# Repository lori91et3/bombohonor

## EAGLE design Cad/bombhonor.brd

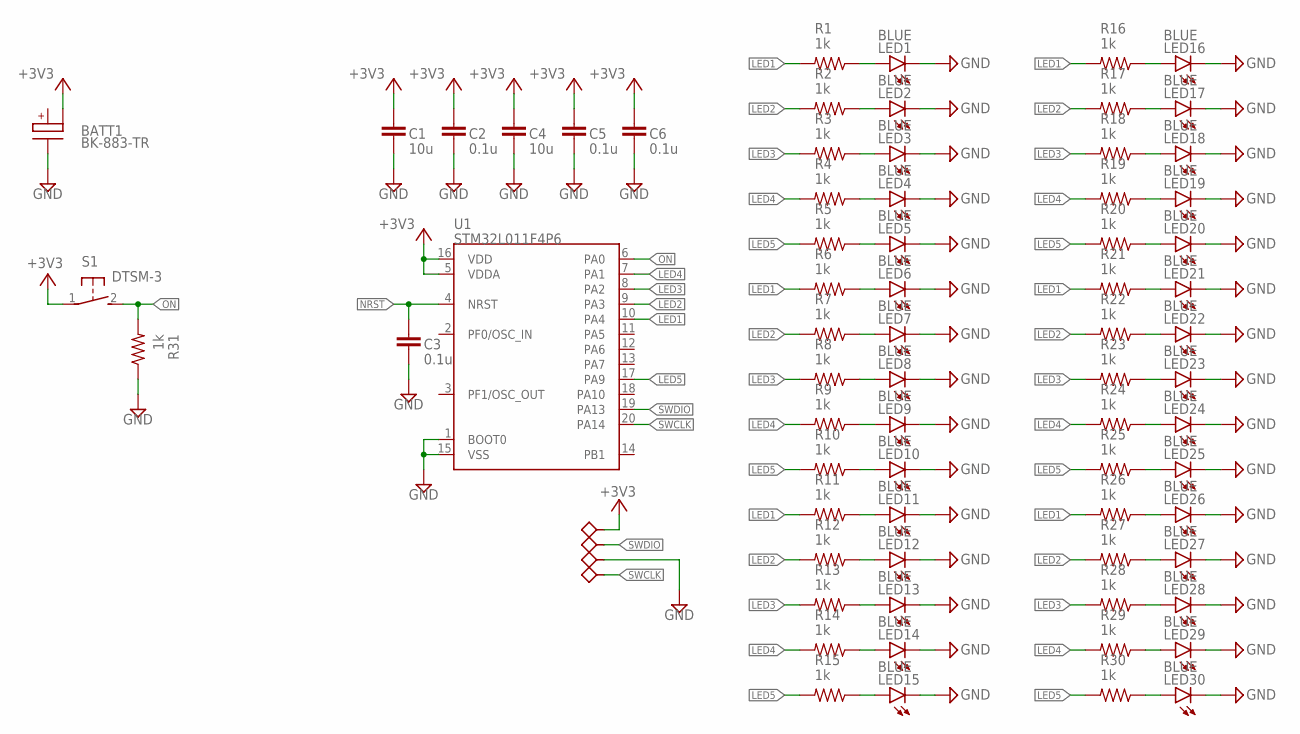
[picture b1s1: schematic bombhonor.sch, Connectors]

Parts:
BATT1: BK-883-TR; PARTNO BK-883-TR
C1, C4: 10u; 0805[2012]; PARTNO CL21A106KQCLRNC
C2, C3, C5, C6: 0.1u; 0603[1608]; PARTNO CL10B104KB8NNNC
LED1, LED2, LED3, LED4, LED5, LED6, LED7, LED8, LED9, LED10, LED11, LED12, LED13, LED14, LED15, LED16, LED17, LED18, LED19, LED20, LED21, LED22, LED23, LED24, LED25, LED26, LED27, LED28, LED29, LED30: BLUE; 1206[3216]BOTTOM_ENTRY; PARTNO LTST-C230TBKT
R1, R2, R3, R4, R5, R6, R7, R8, R9, R10, R11, R12, R13, R14, R15, R16, R17, R18, R19, R20, R21, R22, R23, R24, R25, R26, R27, R28, R29, R30, R31: 1k; 0603[1608]; PARTNO RMCF0603JT1K00
S1: DTSM-3; PARTNO DTSM-3
TP1, TP2, TP3, TP4: TESTPAD2MM; TP-2MM; PARTNO DNP
U1: STM32L011F4P6; TSSOP20; PARTNO STM32L011F4P6

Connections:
+3V3: BATT1.V+2 (V_BATT2), C1.1, C2.1, C4.1, C5.1, C6.1, S1.1, TP1.TP, U1.5 (VDDA), U1.16 (VDD)
GND: BATT1.V- (GND), C1.2, C2.2, C3.2, C4.2, C5.2, C6.2, LED1.K, LED2.K, LED3.K, LED4.K, LED5.K, LED6.K, LED7.K, LED8.K, LED9.K, LED10.K, LED11.K, LED12.K, LED13.K, LED14.K, LED15.K, LED16.K, LED17.K, LED18.K, LED19.K, LED20.K, LED21.K, LED22.K, LED23.K, LED24.K, LED25.K, LED26.K, LED27.K, LED28.K, LED29.K, LED30.K, R31.1, TP3.TP, U1.1 (BOOT0), U1.15 (VSS)
LED1: R1.2, R6.2, R11.2, R16.2, R21.2, R26.2, U1.10 (PA4)
LED2: R2.2, R7.2, R12.2, R17.2, R22.2, R27.2, U1.9 (PA3)
LED3: R3.2, R8.2, R13.2, R18.2, R23.2, R28.2, U1.8 (PA2)
LED4: R4.2, R9.2, R14.2, R19.2, R24.2, R29.2, U1.7 (PA1)
LED5: R5.2, R10.2, R15.2, R20.2, R25.2, R30.2, U1.17 (PA9)
unnamed: LED1.A, R1.1
unnamed: LED2.A, R2.1
unnamed: LED3.A, R3.1
unnamed: LED4.A, R4.1
unnamed: LED5.A, R5.1
unnamed: LED6.A, R6.1
unnamed: LED7.A, R7.1
unnamed: LED8.A, R8.1
unnamed: LED9.A, R9.1
unnamed: LED10.A, R10.1
unnamed: LED11.A, R11.1
unnamed: LED12.A, R12.1
unnamed: LED13.A, R13.1
unnamed: LED14.A, R14.1
unnamed: LED15.A, R15.1
unnamed: LED16.A, R16.1
unnamed: LED17.A, R17.1
unnamed: LED18.A, R18.1
unnamed: LED19.A, R19.1
unnamed: LED20.A, R20.1
unnamed: LED21.A, R21.1
unnamed: LED22.A, R22.1
unnamed: LED23.A, R23.1
unnamed: LED24.A, R24.1
unnamed: LED25.A, R25.1
unnamed: LED26.A, R26.1
unnamed: LED27.A, R27.1
unnamed: LED28.A, R28.1
unnamed: LED29.A, R29.1
unnamed: LED30.A, R30.1
NRST: C3.1, U1.4 (NRST)
ON: R31.2, S1.2, U1.6 (PA0)
SWCLK: TP4.TP, U1.20 (PA14)
SWDIO: TP2.TP, U1.19 (PA13)

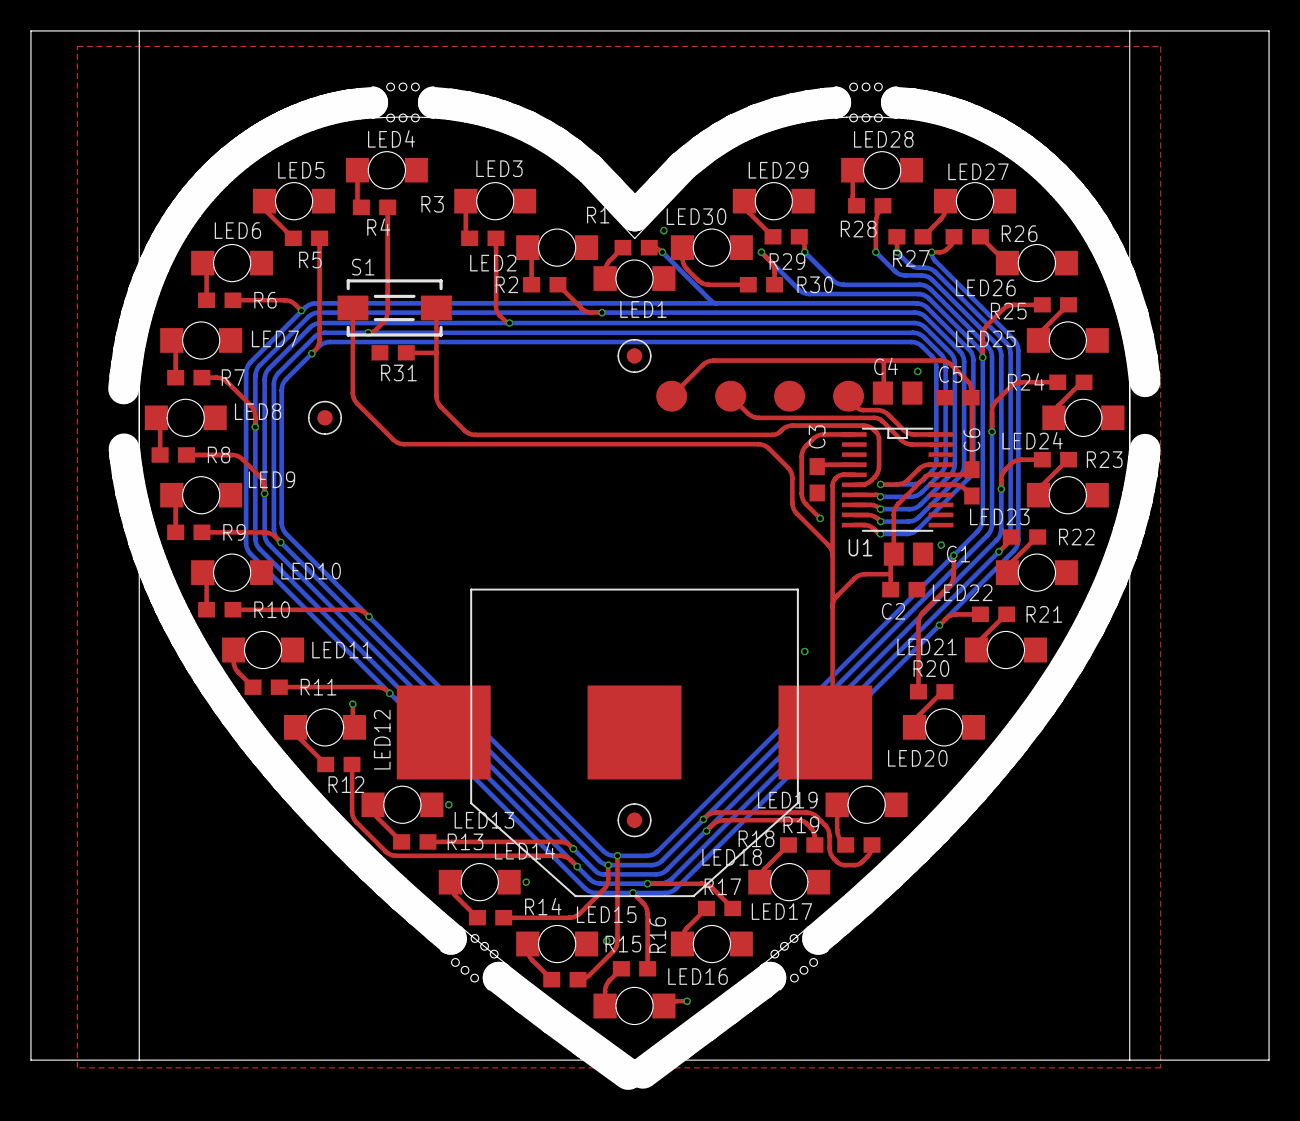
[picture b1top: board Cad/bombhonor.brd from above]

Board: 2 copper layers, 80.0 x 67.4 mm, 82 parts (1 on the bottom side), 41 nets.

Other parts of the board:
1, 2: MOUSE_BITE_2MM
U$1, U$2: MOUSE_BITE_2MM
U$3, U$4, U$5: FIDUCIAL_1MM+2MM+CREAM
U$6: SCRITTA2

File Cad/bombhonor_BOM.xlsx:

Qty | Qty to order | Value | Part Num |  | tot componenti | spesa | 185
4 | 720 | 0.1u | CL10B104KB8NNNC |  | 740
31 | 5580 | 1k | RMCF0603JT1K00 |  | 5735
2 | 360 | 10u | CL21A106KQCLRNC |  | 370
30 | 5400 | BLUE | LTST-C230TBKT |  | 5550
1 | 180 | STM32L011F4P6 | STM32L011F4P6 |  | 185
1 | 180 | BK-883-TR | BK-883-TR |  | 185

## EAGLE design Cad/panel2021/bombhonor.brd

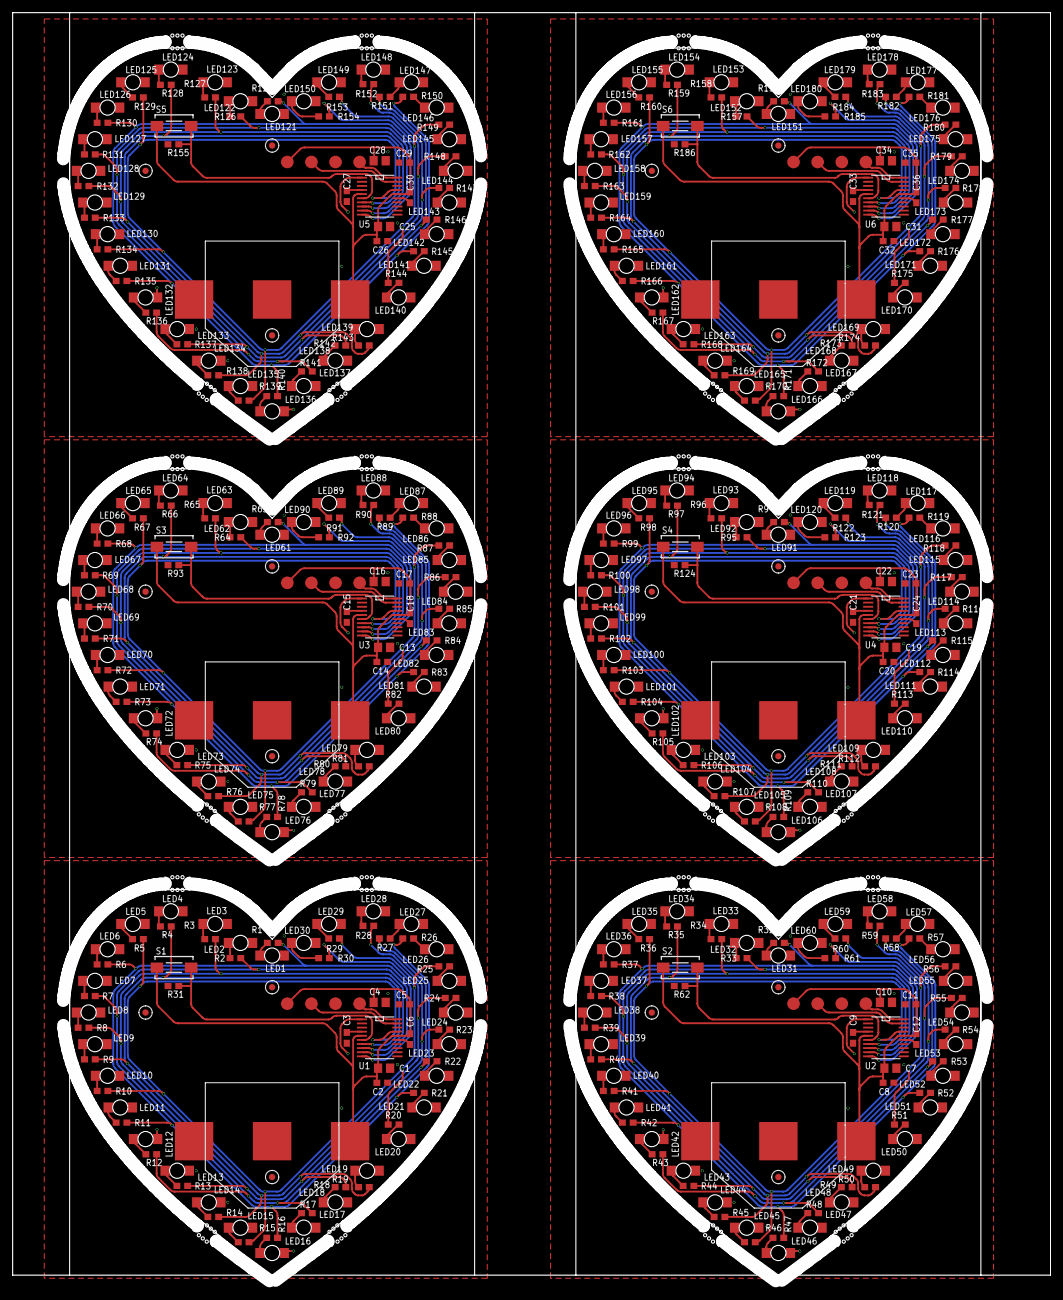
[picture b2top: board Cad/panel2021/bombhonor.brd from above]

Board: 2 copper layers, 164.0 x 200.4 mm, 492 parts (6 on the bottom side), 246 nets.

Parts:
1, 2, 3, 4, 5, 6, 7, 8, 9, 10, 11, 12: MOUSE_BITE_2MM
BATT1, BATT2, BATT3, BATT4, BATT5, BATT6: BK-883-TR
C1, C4, C7, C10, C13, C16, C19, C22, C25, C28, C31, C34: 10u; 0805[2012]
C2, C3, C5, C6, C8, C9, C11, C12, C14, C15, C17, C18, C20, C21, C23, C24, C26, C27, C29, C30, C32, C33, C35, C36: 0.1u; 0603[1608]
LED1, LED2, LED3, LED4, LED5, LED6, LED7, LED8, LED9, LED10, LED11, LED12, LED13, LED14, LED15, LED16, LED17, LED18, LED19, LED20, LED21, LED22, LED23, LED24, LED25, LED26, LED27, LED28, LED29, LED30, LED31, LED32, LED33, LED34, LED35, LED36, LED37, LED38, LED39, LED40, LED41, LED42, LED43, LED44, LED45, LED46, LED47, LED48, LED49, LED50, LED51, LED52, LED53, LED54, LED55, LED56, LED57, LED58, LED59, LED60, LED61, LED62, LED63, LED64, LED65, LED66, LED67, LED68, LED69, LED70, LED71, LED72, LED73, LED74, LED75, LED76, LED77, LED78, LED79, LED80, LED81, LED82, LED83, LED84, LED85, LED86, LED87, LED88, LED89, LED90, LED91, LED92, LED93, LED94, LED95, LED96, LED97, LED98, LED99, LED100, LED101, LED102, LED103, LED104, LED105, LED106, LED107, LED108, LED109, LED110, LED111, LED112, LED113, LED114, LED115, LED116, LED117, LED118, LED119, LED120, LED121, LED122, LED123, LED124, LED125, LED126, LED127, LED128, LED129, LED130, LED131, LED132, LED133, LED134, LED135, LED136, LED137, LED138, LED139, LED140, LED141, LED142, LED143, LED144, LED145, LED146, LED147, LED148, LED149, LED150, LED151, LED152, LED153, LED154, LED155, LED156, LED157, LED158, LED159, LED160, LED161, LED162, LED163, LED164, LED165, LED166, LED167, LED168, LED169, LED170, LED171, LED172, LED173, LED174, LED175, LED176, LED177, LED178, LED179, LED180: BLUE; 1206[3216]BOTTOM_ENTRY
R1, R2, R3, R4, R5, R6, R7, R8, R9, R10, R11, R12, R13, R14, R15, R16, R17, R18, R19, R20, R21, R22, R23, R24, R25, R26, R27, R28, R29, R30, R31, R32, R33, R34, R35, R36, R37, R38, R39, R40, R41, R42, R43, R44, R45, R46, R47, R48, R49, R50, R51, R52, R53, R54, R55, R56, R57, R58, R59, R60, R61, R62, R63, R64, R65, R66, R67, R68, R69, R70, R71, R72, R73, R74, R75, R76, R77, R78, R79, R80, R81, R82, R83, R84, R85, R86, R87, R88, R89, R90, R91, R92, R93, R94, R95, R96, R97, R98, R99, R100, R101, R102, R103, R104, R105, R106, R107, R108, R109, R110, R111, R112, R113, R114, R115, R116, R117, R118, R119, R120, R121, R122, R123, R124, R125, R126, R127, R128, R129, R130, R131, R132, R133, R134, R135, R136, R137, R138, R139, R140, R141, R142, R143, R144, R145, R146, R147, R148, R149, R150, R151, R152, R153, R154, R155, R156, R157, R158, R159, R160, R161, R162, R163, R164, R165, R166, R167, R168, R169, R170, R171, R172, R173, R174, R175, R176, R177, R178, R179, R180, R181, R182, R183, R184, R185, R186: 1k; 0603[1608]
S1, S2, S3, S4, S5, S6: DTSM-3
TP1, TP2, TP3, TP4, TP5, TP6, TP7, TP8, TP9, TP10, TP11, TP12, TP13, TP14, TP15, TP16, TP17, TP18, TP19, TP20, TP21, TP22, TP23, TP24: TESTPAD2MM; TP-2MM
U1, U2, U3, U4, U5, U6: STM32L011F4P6; TSSOP20
U$1, U$2, U$7, U$8, U$13, U$14, U$19, U$20, U$25, U$26, U$31, U$32: MOUSE_BITE_2MM
U$3, U$4, U$5, U$9, U$10, U$11, U$15, U$16, U$17, U$21, U$22, U$23, U$27, U$28, U$29, U$33, U$34, U$35: FIDUCIAL_1MM+2MM+CREAM
U$6, U$12, U$18, U$24, U$30, U$36: SCRITTA2

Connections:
+3V1: BATT2.V+2, C7.1, C8.1, C10.1, C11.1, C12.1, S2.1, TP5.TP, U2.5, U2.16
+3V2: BATT3.V+2, C13.1, C14.1, C16.1, C17.1, C18.1, S3.1, TP9.TP, U3.5, U3.16
+3V3: BATT1.V+2, C1.1, C2.1, C4.1, C5.1, C6.1, S1.1, TP1.TP, U1.5, U1.16
+3V4: BATT4.V+2, C19.1, C20.1, C22.1, C23.1, C24.1, S4.1, TP13.TP, U4.5, U4.16
+3V5: BATT5.V+2, C25.1, C26.1, C28.1, C29.1, C30.1, S5.1, TP17.TP, U5.5, U5.16
+3V6: BATT6.V+2, C31.1, C32.1, C34.1, C35.1, C36.1, S6.1, TP21.TP, U6.5, U6.16
GND: BATT1.V-, C1.2, C2.2, C3.2, C4.2, C5.2, C6.2, LED1.K, LED2.K, LED3.K, LED4.K, LED5.K, LED6.K, LED7.K, LED8.K, LED9.K, LED10.K, LED11.K, LED12.K, LED13.K, LED14.K, LED15.K, LED16.K, LED17.K, LED18.K, LED19.K, LED20.K, LED21.K, LED22.K, LED23.K, LED24.K, LED25.K, LED26.K, LED27.K, LED28.K, LED29.K, LED30.K, R31.1, TP3.TP, U1.1, U1.15
GND1: BATT2.V-, C7.2, C8.2, C9.2, C10.2, C11.2, C12.2, LED31.K, LED32.K, LED33.K, LED34.K, LED35.K, LED36.K, LED37.K, LED38.K, LED39.K, LED40.K, LED41.K, LED42.K, LED43.K, LED44.K, LED45.K, LED46.K, LED47.K, LED48.K, LED49.K, LED50.K, LED51.K, LED52.K, LED53.K, LED54.K, LED55.K, LED56.K, LED57.K, LED58.K, LED59.K, LED60.K, R62.1, TP7.TP, U2.1, U2.15
GND2: BATT3.V-, C13.2, C14.2, C15.2, C16.2, C17.2, C18.2, LED61.K, LED62.K, LED63.K, LED64.K, LED65.K, LED66.K, LED67.K, LED68.K, LED69.K, LED70.K, LED71.K, LED72.K, LED73.K, LED74.K, LED75.K, LED76.K, LED77.K, LED78.K, LED79.K, LED80.K, LED81.K, LED82.K, LED83.K, LED84.K, LED85.K, LED86.K, LED87.K, LED88.K, LED89.K, LED90.K, R93.1, TP11.TP, U3.1, U3.15
GND3: BATT4.V-, C19.2, C20.2, C21.2, C22.2, C23.2, C24.2, LED91.K, LED92.K, LED93.K, LED94.K, LED95.K, LED96.K, LED97.K, LED98.K, LED99.K, LED100.K, LED101.K, LED102.K, LED103.K, LED104.K, LED105.K, LED106.K, LED107.K, LED108.K, LED109.K, LED110.K, LED111.K, LED112.K, LED113.K, LED114.K, LED115.K, LED116.K, LED117.K, LED118.K, LED119.K, LED120.K, R124.1, TP15.TP, U4.1, U4.15
GND4: BATT5.V-, C25.2, C26.2, C27.2, C28.2, C29.2, C30.2, LED121.K, LED122.K, LED123.K, LED124.K, LED125.K, LED126.K, LED127.K, LED128.K, LED129.K, LED130.K, LED131.K, LED132.K, LED133.K, LED134.K, LED135.K, LED136.K, LED137.K, LED138.K, LED139.K, LED140.K, LED141.K, LED142.K, LED143.K, LED144.K, LED145.K, LED146.K, LED147.K, LED148.K, LED149.K, LED150.K, R155.1, TP19.TP, U5.1, U5.15
GND5: BATT6.V-, C31.2, C32.2, C33.2, C34.2, C35.2, C36.2, LED151.K, LED152.K, LED153.K, LED154.K, LED155.K, LED156.K, LED157.K, LED158.K, LED159.K, LED160.K, LED161.K, LED162.K, LED163.K, LED164.K, LED165.K, LED166.K, LED167.K, LED168.K, LED169.K, LED170.K, LED171.K, LED172.K, LED173.K, LED174.K, LED175.K, LED176.K, LED177.K, LED178.K, LED179.K, LED180.K, R186.1, TP23.TP, U6.1, U6.15
LED1: R1.2, R6.2, R11.2, R16.2, R21.2, R26.2, U1.10
LED2: R2.2, R7.2, R12.2, R17.2, R22.2, R27.2, U1.9
LED3: R3.2, R8.2, R13.2, R18.2, R23.2, R28.2, U1.8
LED4: R4.2, R9.2, R14.2, R19.2, R24.2, R29.2, U1.7
LED5: R5.2, R10.2, R15.2, R20.2, R25.2, R30.2, U1.17
LED6: R32.2, R37.2, R42.2, R47.2, R52.2, R57.2, U2.10
LED7: R33.2, R38.2, R43.2, R48.2, R53.2, R58.2, U2.9
LED8: R34.2, R39.2, R44.2, R49.2, R54.2, R59.2, U2.8
LED9: R35.2, R40.2, R45.2, R50.2, R55.2, R60.2, U2.7
LED10: R36.2, R41.2, R46.2, R51.2, R56.2, R61.2, U2.17
LED11: R63.2, R68.2, R73.2, R78.2, R83.2, R88.2, U3.10
LED12: R64.2, R69.2, R74.2, R79.2, R84.2, R89.2, U3.9
LED13: R65.2, R70.2, R75.2, R80.2, R85.2, R90.2, U3.8
LED14: R66.2, R71.2, R76.2, R81.2, R86.2, R91.2, U3.7
LED15: R67.2, R72.2, R77.2, R82.2, R87.2, R92.2, U3.17
LED16: R94.2, R99.2, R104.2, R109.2, R114.2, R119.2, U4.10
LED17: R95.2, R100.2, R105.2, R110.2, R115.2, R120.2, U4.9
LED18: R96.2, R101.2, R106.2, R111.2, R116.2, R121.2, U4.8
LED19: R97.2, R102.2, R107.2, R112.2, R117.2, R122.2, U4.7
LED20: R98.2, R103.2, R108.2, R113.2, R118.2, R123.2, U4.17
LED21: R125.2, R130.2, R135.2, R140.2, R145.2, R150.2, U5.10
LED22: R126.2, R131.2, R136.2, R141.2, R146.2, R151.2, U5.9
LED23: R127.2, R132.2, R137.2, R142.2, R147.2, R152.2, U5.8
LED24: R128.2, R133.2, R138.2, R143.2, R148.2, R153.2, U5.7
LED25: R129.2, R134.2, R139.2, R144.2, R149.2, R154.2, U5.17
LED26: R156.2, R161.2, R166.2, R171.2, R176.2, R181.2, U6.10
LED27: R157.2, R162.2, R167.2, R172.2, R177.2, R182.2, U6.9
LED28: R158.2, R163.2, R168.2, R173.2, R178.2, R183.2, U6.8
LED29: R159.2, R164.2, R169.2, R174.2, R179.2, R184.2, U6.7
LED30: R160.2, R165.2, R170.2, R175.2, R180.2, R185.2, U6.17
unnamed: LED1.A, R1.1
unnamed: LED2.A, R2.1
unnamed: LED3.A, R3.1
unnamed: LED4.A, R4.1
unnamed: LED5.A, R5.1
unnamed: LED6.A, R6.1
unnamed: LED7.A, R7.1
unnamed: LED8.A, R8.1
unnamed: LED9.A, R9.1
unnamed: LED10.A, R10.1
unnamed: LED11.A, R11.1
unnamed: LED12.A, R12.1
unnamed: LED13.A, R13.1
unnamed: LED14.A, R14.1
unnamed: LED15.A, R15.1
unnamed: LED16.A, R16.1
unnamed: LED17.A, R17.1
unnamed: LED18.A, R18.1
unnamed: LED19.A, R19.1
unnamed: LED20.A, R20.1
unnamed: LED21.A, R21.1
unnamed: LED22.A, R22.1
unnamed: LED23.A, R23.1
unnamed: LED24.A, R24.1
unnamed: LED25.A, R25.1
unnamed: LED26.A, R26.1
unnamed: LED27.A, R27.1
unnamed: LED28.A, R28.1
unnamed: LED29.A, R29.1
unnamed: LED30.A, R30.1
unnamed: LED31.A, R32.1
unnamed: LED32.A, R33.1
unnamed: LED33.A, R34.1
unnamed: LED34.A, R35.1
unnamed: LED35.A, R36.1
unnamed: LED36.A, R37.1
unnamed: LED37.A, R38.1
unnamed: LED38.A, R39.1
unnamed: LED39.A, R40.1
unnamed: LED40.A, R41.1
unnamed: LED41.A, R42.1
unnamed: LED42.A, R43.1
unnamed: LED43.A, R44.1
unnamed: LED44.A, R45.1
unnamed: LED45.A, R46.1
unnamed: LED46.A, R47.1
unnamed: LED47.A, R48.1
unnamed: LED48.A, R49.1
unnamed: LED49.A, R50.1
unnamed: LED50.A, R51.1
unnamed: LED51.A, R52.1
unnamed: LED52.A, R53.1
unnamed: LED53.A, R54.1
unnamed: LED54.A, R55.1
unnamed: LED55.A, R56.1
unnamed: LED56.A, R57.1
unnamed: LED57.A, R58.1
unnamed: LED58.A, R59.1
unnamed: LED59.A, R60.1
unnamed: LED60.A, R61.1
unnamed: LED61.A, R63.1
unnamed: LED62.A, R64.1
unnamed: LED63.A, R65.1
unnamed: LED64.A, R66.1
unnamed: LED65.A, R67.1
unnamed: LED66.A, R68.1
unnamed: LED67.A, R69.1
unnamed: LED68.A, R70.1
unnamed: LED69.A, R71.1
unnamed: LED70.A, R72.1
unnamed: LED71.A, R73.1
unnamed: LED72.A, R74.1
unnamed: LED73.A, R75.1
unnamed: LED74.A, R76.1
unnamed: LED75.A, R77.1
unnamed: LED76.A, R78.1
unnamed: LED77.A, R79.1
unnamed: LED78.A, R80.1
unnamed: LED79.A, R81.1
unnamed: LED80.A, R82.1
unnamed: LED81.A, R83.1
unnamed: LED82.A, R84.1
unnamed: LED83.A, R85.1
unnamed: LED84.A, R86.1
unnamed: LED85.A, R87.1
unnamed: LED86.A, R88.1
unnamed: LED87.A, R89.1
unnamed: LED88.A, R90.1
unnamed: LED89.A, R91.1
unnamed: LED90.A, R92.1
unnamed: LED91.A, R94.1
unnamed: LED92.A, R95.1
unnamed: LED93.A, R96.1
unnamed: LED94.A, R97.1
unnamed: LED95.A, R98.1
unnamed: LED96.A, R99.1
unnamed: LED97.A, R100.1
unnamed: LED98.A, R101.1
unnamed: LED99.A, R102.1
unnamed: LED100.A, R103.1
unnamed: LED101.A, R104.1
unnamed: LED102.A, R105.1
unnamed: LED103.A, R106.1
unnamed: LED104.A, R107.1
unnamed: LED105.A, R108.1
unnamed: LED106.A, R109.1
unnamed: LED107.A, R110.1
unnamed: LED108.A, R111.1
unnamed: LED109.A, R112.1
unnamed: LED110.A, R113.1
unnamed: LED111.A, R114.1
unnamed: LED112.A, R115.1
unnamed: LED113.A, R116.1
unnamed: LED114.A, R117.1
unnamed: LED115.A, R118.1
unnamed: LED116.A, R119.1
unnamed: LED117.A, R120.1
unnamed: LED118.A, R121.1
unnamed: LED119.A, R122.1
unnamed: LED120.A, R123.1
unnamed: LED121.A, R125.1
unnamed: LED122.A, R126.1
unnamed: LED123.A, R127.1
unnamed: LED124.A, R128.1
unnamed: LED125.A, R129.1
unnamed: LED126.A, R130.1
unnamed: LED127.A, R131.1
unnamed: LED128.A, R132.1
unnamed: LED129.A, R133.1
unnamed: LED130.A, R134.1
unnamed: LED131.A, R135.1
unnamed: LED132.A, R136.1
unnamed: LED133.A, R137.1
unnamed: LED134.A, R138.1
unnamed: LED135.A, R139.1
unnamed: LED136.A, R140.1
unnamed: LED137.A, R141.1
unnamed: LED138.A, R142.1
unnamed: LED139.A, R143.1
unnamed: LED140.A, R144.1
unnamed: LED141.A, R145.1
unnamed: LED142.A, R146.1
unnamed: LED143.A, R147.1
unnamed: LED144.A, R148.1
unnamed: LED145.A, R149.1
unnamed: LED146.A, R150.1
unnamed: LED147.A, R151.1
unnamed: LED148.A, R152.1
unnamed: LED149.A, R153.1
unnamed: LED150.A, R154.1
unnamed: LED151.A, R156.1
unnamed: LED152.A, R157.1
unnamed: LED153.A, R158.1
unnamed: LED154.A, R159.1
unnamed: LED155.A, R160.1
unnamed: LED156.A, R161.1
unnamed: LED157.A, R162.1
unnamed: LED158.A, R163.1
unnamed: LED159.A, R164.1
unnamed: LED160.A, R165.1
unnamed: LED161.A, R166.1
unnamed: LED162.A, R167.1
unnamed: LED163.A, R168.1
unnamed: LED164.A, R169.1
unnamed: LED165.A, R170.1
unnamed: LED166.A, R171.1
unnamed: LED167.A, R172.1
unnamed: LED168.A, R173.1
unnamed: LED169.A, R174.1
unnamed: LED170.A, R175.1
unnamed: LED171.A, R176.1
unnamed: LED172.A, R177.1
unnamed: LED173.A, R178.1
unnamed: LED174.A, R179.1
unnamed: LED175.A, R180.1
unnamed: LED176.A, R181.1
unnamed: LED177.A, R182.1
unnamed: LED178.A, R183.1
unnamed: LED179.A, R184.1
unnamed: LED180.A, R185.1
NRST: C3.1, U1.4
NRST1: C9.1, U2.4
NRST2: C15.1, U3.4
NRST3: C21.1, U4.4
NRST4: C27.1, U5.4
NRST5: C33.1, U6.4
ON: R31.2, S1.2, U1.6
ON1: R62.2, S2.2, U2.6
ON2: R93.2, S3.2, U3.6
ON3: R124.2, S4.2, U4.6
ON4: R155.2, S5.2, U5.6
ON5: R186.2, S6.2, U6.6
SWCLK: TP4.TP, U1.20
SWCLK1: TP8.TP, U2.20
SWCLK2: TP12.TP, U3.20
SWCLK3: TP16.TP, U4.20
SWCLK4: TP20.TP, U5.20
SWCLK5: TP24.TP, U6.20
SWDIO: TP2.TP, U1.19
SWDIO1: TP6.TP, U2.19
SWDIO2: TP10.TP, U3.19
SWDIO3: TP14.TP, U4.19
SWDIO4: TP18.TP, U5.19
SWDIO5: TP22.TP, U6.19

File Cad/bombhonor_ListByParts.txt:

Part	Value	Attributes	Package	Description	Part Number	Mfg Name	VID	Vendor Part Num	Description	Pkg Code	Customer Ref	Library	Footprint	Status	XREF
BATT1	BK-883-TR		BK-883-TR		BK-883-TR	*	*	*	*	*	*	*	*	*	*
C1	10u		0805[2012]		CL21A106KQCLRNC	*	*	*	*	*	*	*	*	*	*
C2	0.1u		0603[1608]		CL10B104KB8NNNC	*	*	*	*	*	*	*	*	*	*
C3	0.1u		0603[1608]		CL10B104KB8NNNC	*	*	*	*	*	*	*	*	*	*
C4	10u		0805[2012]		CL21A106KQCLRNC	*	*	*	*	*	*	*	*	*	*
C5	0.1u		0603[1608]		CL10B104KB8NNNC	*	*	*	*	*	*	*	*	*	*
C6	0.1u		0603[1608]		CL10B104KB8NNNC	*	*	*	*	*	*	*	*	*	*
CN1	HEADER4X1_2MM_SMD		HEADER4X1_2MM_SMD		2PH1-04-UA-SMT-B	*	*	*	*	*	*	*	*	*	*
CN2	TR1-01		MAROGNATA		TR1-01	*	*	*	*	*	*	*	*	*	*
LED1	RED		1206[3216]BOTTOM_ENTRY		LTST-C230KRKT	*	*	*	*	*	*	*	*	*	*
LED2	RED		1206[3216]BOTTOM_ENTRY		LTST-C230KRKT	*	*	*	*	*	*	*	*	*	*
LED3	RED		1206[3216]BOTTOM_ENTRY		LTST-C230KRKT	*	*	*	*	*	*	*	*	*	*
LED4	RED		1206[3216]BOTTOM_ENTRY		LTST-C230KRKT	*	*	*	*	*	*	*	*	*	*
LED5	RED		1206[3216]BOTTOM_ENTRY		LTST-C230KRKT	*	*	*	*	*	*	*	*	*	*
LED6	RED		1206[3216]BOTTOM_ENTRY		LTST-C230KRKT	*	*	*	*	*	*	*	*	*	*
LED7	RED		1206[3216]BOTTOM_ENTRY		LTST-C230KRKT	*	*	*	*	*	*	*	*	*	*
LED8	RED		1206[3216]BOTTOM_ENTRY		LTST-C230KRKT	*	*	*	*	*	*	*	*	*	*
LED9	RED		1206[3216]BOTTOM_ENTRY		LTST-C230KRKT	*	*	*	*	*	*	*	*	*	*
LED10	RED		1206[3216]BOTTOM_ENTRY		LTST-C230KRKT	*	*	*	*	*	*	*	*	*	*
LED11	RED		1206[3216]BOTTOM_ENTRY		LTST-C230KRKT	*	*	*	*	*	*	*	*	*	*
LED12	RED		1206[3216]BOTTOM_ENTRY		LTST-C230KRKT	*	*	*	*	*	*	*	*	*	*
LED13	RED		1206[3216]BOTTOM_ENTRY		LTST-C230KRKT	*	*	*	*	*	*	*	*	*	*
LED14	RED		1206[3216]BOTTOM_ENTRY		LTST-C230KRKT	*	*	*	*	*	*	*	*	*	*
LED15	RED		1206[3216]BOTTOM_ENTRY		LTST-C230KRKT	*	*	*	*	*	*	*	*	*	*
LED16	RED		1206[3216]BOTTOM_ENTRY		LTST-C230KRKT	*	*	*	*	*	*	*	*	*	*
LED17	RED		1206[3216]BOTTOM_ENTRY		LTST-C230KRKT	*	*	*	*	*	*	*	*	*	*
LED18	RED		1206[3216]BOTTOM_ENTRY		LTST-C230KRKT	*	*	*	*	*	*	*	*	*	*
LED19	RED		1206[3216]BOTTOM_ENTRY		LTST-C230KRKT	*	*	*	*	*	*	*	*	*	*
LED20	RED		1206[3216]BOTTOM_ENTRY		LTST-C230KRKT	*	*	*	*	*	*	*	*	*	*
LED21	RED		1206[3216]BOTTOM_ENTRY		LTST-C230KRKT	*	*	*	*	*	*	*	*	*	*
LED22	RED		1206[3216]BOTTOM_ENTRY		LTST-C230KRKT	*	*	*	*	*	*	*	*	*	*
LED23	RED		1206[3216]BOTTOM_ENTRY		LTST-C230KRKT	*	*	*	*	*	*	*	*	*	*
LED24	RED		1206[3216]BOTTOM_ENTRY		LTST-C230KRKT	*	*	*	*	*	*	*	*	*	*
LED25	RED		1206[3216]BOTTOM_ENTRY		LTST-C230KRKT	*	*	*	*	*	*	*	*	*	*
LED26	RED		1206[3216]BOTTOM_ENTRY		LTST-C230KRKT	*	*	*	*	*	*	*	*	*	*
LED27	RED		1206[3216]BOTTOM_ENTRY		LTST-C230KRKT	*	*	*	*	*	*	*	*	*	*
LED28	RED		1206[3216]BOTTOM_ENTRY		LTST-C230KRKT	*	*	*	*	*	*	*	*	*	*
LED29	RED		1206[3216]BOTTOM_ENTRY		LTST-C230KRKT	*	*	*	*	*	*	*	*	*	*
LED30	RED		1206[3216]BOTTOM_ENTRY		LTST-C230KRKT	*	*	*	*	*	*	*	*	*	*
R1	1k		0603[1608]		RMCF0603JT1K00	*	*	*	*	*	*	*	*	*	*
R2	1k		0603[1608]		RMCF0603JT1K00	*	*	*	*	*	*	*	*	*	*
R3	1k		0603[1608]		RMCF0603JT1K00	*	*	*	*	*	*	*	*	*	*
R4	1k		0603[1608]		RMCF0603JT1K00	*	*	*	*	*	*	*	*	*	*
R5	1k		0603[1608]		RMCF0603JT1K00	*	*	*	*	*	*	*	*	*	*
R6	1k		0603[1608]		RMCF0603JT1K00	*	*	*	*	*	*	*	*	*	*
R7	1k		0603[1608]		RMCF0603JT1K00	*	*	*	*	*	*	*	*	*	*
R8	1k		0603[1608]		RMCF0603JT1K00	*	*	*	*	*	*	*	*	*	*
R9	1k		0603[1608]		RMCF0603JT1K00	*	*	*	*	*	*	*	*	*	*
R10	1k		0603[1608]		RMCF0603JT1K00	*	*	*	*	*	*	*	*	*	*
R11	1k		0603[1608]		RMCF0603JT1K00	*	*	*	*	*	*	*	*	*	*
R12	1k		0603[1608]		RMCF0603JT1K00	*	*	*	*	*	*	*	*	*	*
R13	1k		0603[1608]		RMCF0603JT1K00	*	*	*	*	*	*	*	*	*	*
R14	1k		0603[1608]		RMCF0603JT1K00	*	*	*	*	*	*	*	*	*	*
R15	1k		0603[1608]		RMCF0603JT1K00	*	*	*	*	*	*	*	*	*	*
R16	1k		0603[1608]		RMCF0603JT1K00	*	*	*	*	*	*	*	*	*	*
R17	1k		0603[1608]		RMCF0603JT1K00	*	*	*	*	*	*	*	*	*	*
R18	1k		0603[1608]		RMCF0603JT1K00	*	*	*	*	*	*	*	*	*	*
R19	1k		0603[1608]		RMCF0603JT1K00	*	*	*	*	*	*	*	*	*	*
R20	1k		0603[1608]		RMCF0603JT1K00	*	*	*	*	*	*	*	*	*	*
R21	1k		0603[1608]		RMCF0603JT1K00	*	*	*	*	*	*	*	*	*	*
R22	1k		0603[1608]		RMCF0603JT1K00	*	*	*	*	*	*	*	*	*	*
R23	1k		0603[1608]		RMCF0603JT1K00	*	*	*	*	*	*	*	*	*	*
R24	1k		0603[1608]		RMCF0603JT1K00	*	*	*	*	*	*	*	*	*	*
R25	1k		0603[1608]		RMCF0603JT1K00	*	*	*	*	*	*	*	*	*	*
R26	1k		0603[1608]		RMCF0603JT1K00	*	*	*	*	*	*	*	*	*	*
R27	1k		0603[1608]		RMCF0603JT1K00	*	*	*	*	*	*	*	*	*	*
R28	1k		0603[1608]		RMCF0603JT1K00	*	*	*	*	*	*	*	*	*	*
R29	1k		0603[1608]		RMCF0603JT1K00	*	*	*	*	*	*	*	*	*	*
R30	1k		0603[1608]		RMCF0603JT1K00	*	*	*	*	*	*	*	*	*	*
R31	1k		0603[1608]		RMCF0603JT1K00	*	*	*	*	*	*	*	*	*	*
U1	STM32L011F4P6		TSSOP20		STM32F030F4P6TR	*	*	*	*	*	*	*	*	*	*

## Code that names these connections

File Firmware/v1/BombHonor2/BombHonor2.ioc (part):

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Mcu.Name=STM32L011F(3-4)Px
Mcu.Package=TSSOP20
Mcu.UserName=STM32L011F3Px
PA0-CK_IN.GPIOParameters=GPIO_Label
PA0-CK_IN.GPIO_Label=ON
PA0-CK_IN.Mode=SYS_WakeUp0
PA0-CK_IN.Signal=SYS_WKUP1
PA1.GPIOParameters=GPIO_Label
PA1.GPIO_Label=LED4
PA1.Signal=GPIO_Output
PA13.Mode=Serial_Wire
PA13.Signal=SYS_SWDIO
PA14.Mode=Serial_Wire
PA14.Signal=SYS_SWCLK
PA2.GPIOParameters=GPIO_Label
PA2.GPIO_Label=LED3
PA2.Signal=GPIO_Output
PA3.GPIOParameters=GPIO_Label
PA3.GPIO_Label=LED2
PA3.Signal=GPIO_Output
PA4.GPIOParameters=GPIO_Label
PA4.GPIO_Label=LED1
PA4.Signal=GPIO_Output
PA9.GPIOParameters=GPIO_Label
PA9.GPIO_Label=LED5
PA9.Signal=GPIO_Output
RCC.HSE_VALUE=8000000
RCC.SYSCLKFreq_VALUE=16000000
RCC.SYSCLKSource=RCC_SYSCLKSOURCE_PLLCLK
board=custom

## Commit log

2019-12-14 Disegnata la forma di cuore nel dimension del PCB
2019-12-14 Aggiunti tutti i pezzi tranne il connettore batteria ed il pulsante, domani fine schematico e calcolo costo per sapere se si fa o si muore
2019-12-15 Finito lo schematico. Mancano i parno per i passivi.
2019-12-17 Finito lo sbroglio della scheda
2019-12-17 stessa cosa
2019-12-17 Terminata la BOM, da calcolare la spesa totale
2019-12-18 Messi a posto nomi e dettagli. La bom costa 3.85€
2019-12-18 Messe a posto le piste
2020-01-14 Aggiunto firmware base che si illumina. Messa a posto la bom e scritto commenti con partno sullo schematico
2020-01-14 Aggiunte cose da comprare allo schematico Ridotto la velocità di blinking nel FW
2020-01-18 Messi i testpad sul PCB invece che il connettore Creato il primo supporto da provare a stampare
2020-01-19 Secondo tentativo bomboniera
2020-01-19 Terzo supporto, speriamo che sia l'ultimo
2020-01-19 messo a posto l'stl
2020-01-21 Modificata scheda per avere i pin a posto con l'STM32L011. Creata fantasia su vecchia scheda. Aggiunto codice nuovo micro
2020-01-25 Tolto il bug, ora va in sleep tutte le volte correttamente e si sveglia quando si clicca il pulsante
2020-01-25 Aggiunta anche rotazione ccw
2020-01-25 Aggiunto supporto V4
2020-01-26 Terminata la versione 4 del supporto con i ganci per i confetti. Forse è da accorciare ma si fa a tempo
2020-01-26 Inspessito il davanti, supporto 5 completato
2020-01-26 corretto il supporto5
2020-01-27 Iniziata a mettere aposto la scheda. cambiato pulsante. il reset non ci sta
2020-01-27 aggiunte scritt alle librerie
2020-01-27 Aggiustata scritta e messi a posto un po' di pistolini
2020-01-28 Aggiunta libreria lasciata indietro e messo a posto supporto. Speriamo che sia l'ultimo
2020-02-05 Ridotta l'altezza dell'asola e lo spessore interno del PCB
2020-02-14 Aggiunta altra scritta
2020-02-14 Aggiunto font della scritta
2020-02-14 Messa a posto la bom, creato excel e stime di costo
2020-02-15 Ultimato PCB, si procede con il pannello
2020-02-15 Pannellizzato ogni cosa
2020-02-15 messo a posto pannello
2020-03-01 cambiati part number led
2020-06-26 messa a posto la roba per il 2021
2021-01-23 Rimossa data
2022-02-13 Ultimo commit
